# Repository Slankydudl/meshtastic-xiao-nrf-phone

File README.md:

<div align="center" markdown="1">

<h1>Meshtastic T9 Phone</h1>

</div>

## Overview
This repo contains all the needed PCB manufacturing files and 3D print files to turn your SEED XIAO nRF52840 & Wio-SX1262 Kit into the phone above... provided you're handy with a soldering iron.

</div>

### Additional Parts

- **[SEEED XIAO Kit](https://www.seeedstudio.com/XIAO-nRF52840-Wio-SX1262-Kit-for-Meshtastic-p-6400.html)**
- **[1.3" OLED](https://www.aliexpress.com/item/1005008934254841.html?spm=a2g0o.order_list.order_list_main.34.63fd1802lfZtmT)**
- **[2000mAh Battery](https://www.aliexpress.com/item/1005009571773727.html?spm=a2g0o.order_list.order_list_main.44.63fd1802lfZtmT)**

### Key Map

TBC

</div>

### Links
- **[Firmware](https://github.com/Slankydudl/firmware/tree/TCA8418_optimisations)** - Meshtastic firmware fork.
- **[Standalone Keypad](https://github.com/Slankydudl/T9-Keypad-Module)** - If you just want the keypad.
- **[onshape model](https://cad.onshape.com/documents/3c51ee3a5f6604343e4842f4/w/fb2a1c1f9218dcd275d16dea/e/b00e8f57d3ea05ff20d6055f?renderMode=0&uiState=6ab0b72fc6c97693bf5fc8d2)** - If you want to copy and edit the 3D print in onshape.

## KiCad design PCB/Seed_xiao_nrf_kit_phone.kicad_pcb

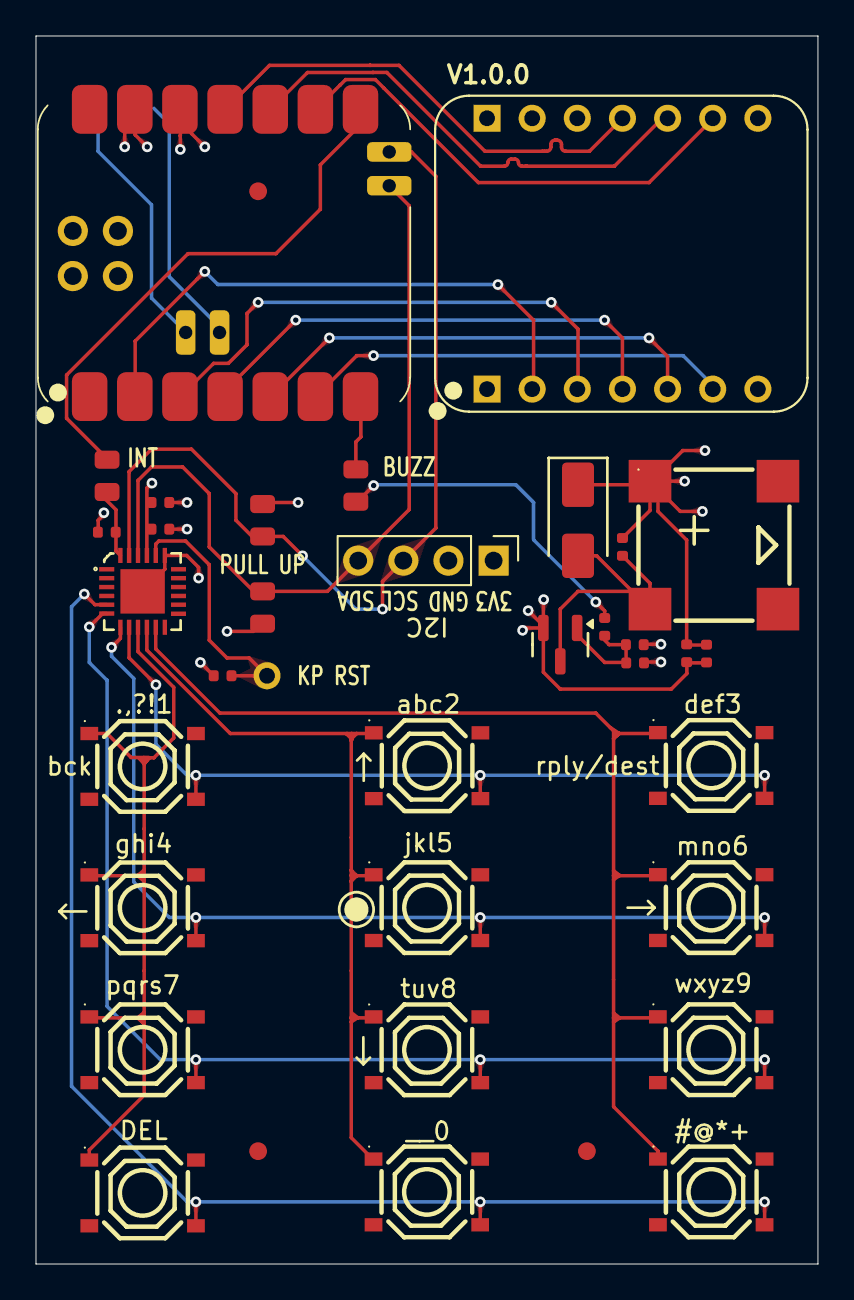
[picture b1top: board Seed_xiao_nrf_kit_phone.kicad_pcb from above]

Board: 4 copper layers, 44.0 x 69.1 mm, 33 parts (0 on the bottom side), 26 nets.

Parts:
BUZZER1: MLT-8530; easyeda2kicad__BUZ-SMD_4P-L8.5-W8.5-P8.50-BR_d8af27ad9a
C1, C12: 10uF; PCM_JLCPCB__C_0402_5b7475e20d
C2, C10, C11: 100nF; PCM_JLCPCB__C_0402_5b7475e20d
C13: 22pF; PCM_JLCPCB__C_0402_5b7475e20d
D2: SS14; PCM_JLCPCB__D_SMA_5ba77312ee
J1: 4pin header; Self_Made__4Pin header_d1808ed7c5
Q2: AO3400A; PCM_JLCPCB__Q_SOT-23_0535f4caa0
R1, R2: 4.7kΩ; PCM_JLCPCB__R_0805_38555c8e56
R3, R4: 10kΩ; PCM_JLCPCB__R_0402_50b788cd01
R12: 100Ω; PCM_JLCPCB__R_0402_50b788cd01
R13: 100kΩ; PCM_JLCPCB__R_0402_50b788cd01
R14, R15: 0Ω; PCM_JLCPCB__R_0805_38555c8e56
SW1, SW2, SW3, SW4, SW5, SW6, SW7, SW8, SW9, SW10, SW11, SW12: TS-1187A-B-A-B; easyeda2kicad__TS-1187A-B-A-B_2a0d7a9c99
U1: TCA8418RTWR; easyeda2kicad__TCA8418RTWR_3b4f66023a
U2: XIAO-nRF52840-SMD; XIAO_Series_Footprints__XIAO-nRF52840-SMD_Vias_a8f4777abb
U9: WIO-SX1262-DIP; Self_Made__WIO-SX1262-DIP_83e7a100c9

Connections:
+3V3: BUZZER1.1 (+), C1.1, C2.1, C10.1, C11.1, C12.1, D2.1, J1.1, R1.1, R2.1, R3.1, R4.1, U1.21 (VCC), U2.12 (3V3), U9.12 (3V3)
/Buzz: R12.2, R14.1
/Column_0: SW1.1 (A), SW2.1 (A), SW3.1 (A), SW4.1 (A), U1.9 (COL0)
/Column_1: SW5.1 (A), SW6.1 (A), SW7.1 (A), SW8.1 (A), U1.10 (COL1)
/Column_2: SW9.1 (A), SW10.1 (A), SW11.1 (A), SW12.1 (A), U1.11 (COL2)
/INT: R3.2, R15.1, U1.24 (~INT)
/RST: R4.2, U1.20 (~RESET)
/Row_0: SW1.4 (D), SW5.4 (D), SW9.4 (D), U1.8 (ROW0)
/Row_1: SW2.4 (D), SW6.4 (D), SW10.4 (D), U1.7 (ROW1)
/Row_2: SW3.4 (D), SW7.4 (D), SW11.4 (D), U1.6 (ROW2)
/Row_3: SW4.4 (D), SW8.4 (D), SW12.4 (D), U1.5 (ROW3)
/SCL: J1.3, R1.2, U1.23 (SCL), U2.35 (P0.10_NFC2)
/SDA: J1.4, R2.2, U1.22 (SDA), U2.34 (P0.09_NFC1)
GND: C1.2, C2.2, C11.2, C12.2, C13.2, J1.2, Q2.2 (S), R13.2, U1.19 (GND), U1.25 (EP), U2.13 (GND), U9.13 (GND)
unnamed: BUZZER1.2, C10.2, D2.2, Q2.3 (D)
unnamed: C13.1, Q2.1 (G), R12.1, R13.1
unnamed: U2.2 (P0.03_A1_D1), U9.2 (DIO1)
unnamed: U2.5 (P0.04_A4_D4_SDA), U9.5 (NSS)
unnamed: U2.6 (P0.05_A5_D5_SCL), U9.6 (RF_SW)
unnamed: U2.3 (P0.28_A2_D2), U9.3 (RST)
unnamed: U2.4 (P0.29_A3_D3), U9.4 (BUSY)
unnamed: R14.2, U2.7 (P1.11_D6_TX)
unnamed: R15.2, U2.8 (P1.12_D7_RX)
unnamed: U2.9 (P1.13_D8_SCK), U9.9 (SCK)
unnamed: U2.10 (P1.14_D9_MISO), U9.10 (MISO)
unnamed: U2.11 (P1.15_D10_MOSI), U9.11 (MOSI)

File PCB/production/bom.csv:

Designator,Footprint,Quantity,Value,LCSC Part #
"_6, _5",,2,,
BUZZER1,easyeda2kicad__BUZ-SMD_4P-L8.5-W8.5-P8.50-BR_d8af27ad9a,1,MLT-8530,C94599
"C1, C12",PCM_JLCPCB__C_0402_5b7475e20d,2,10uF,C15525
"C10, C11, C2",PCM_JLCPCB__C_0402_5b7475e20d,3,100nF,C1525
C13,PCM_JLCPCB__C_0402_5b7475e20d,1,22pF,C1555
D2,PCM_JLCPCB__D_SMA_5ba77312ee,1,SS14,C2480
Q2,PCM_JLCPCB__Q_SOT-23_0535f4caa0,1,AO3400A,C20917
"R1, R2",PCM_JLCPCB__R_0805_38555c8e56,2,4.7kΩ,C17673
R12,PCM_JLCPCB__R_0402_50b788cd01,1,100Ω,C25076
R13,PCM_JLCPCB__R_0402_50b788cd01,1,100kΩ,C25741
"R14, R15",PCM_JLCPCB__R_0805_38555c8e56,2,0Ω,C17477
"R3, R4",PCM_JLCPCB__R_0402_50b788cd01,2,10kΩ,C25744
"SW1, SW10, SW11, SW12, SW2, SW3, SW4, SW5, SW6, SW7, SW8, SW9",easyeda2kicad__TS-1187A-B-A-B_2a0d7a9c99,12,TS-1187A-B-A-B,C318884
U1,easyeda2kicad__TCA8418RTWR_3b4f66023a,1,TCA8418RTWR,C138713
